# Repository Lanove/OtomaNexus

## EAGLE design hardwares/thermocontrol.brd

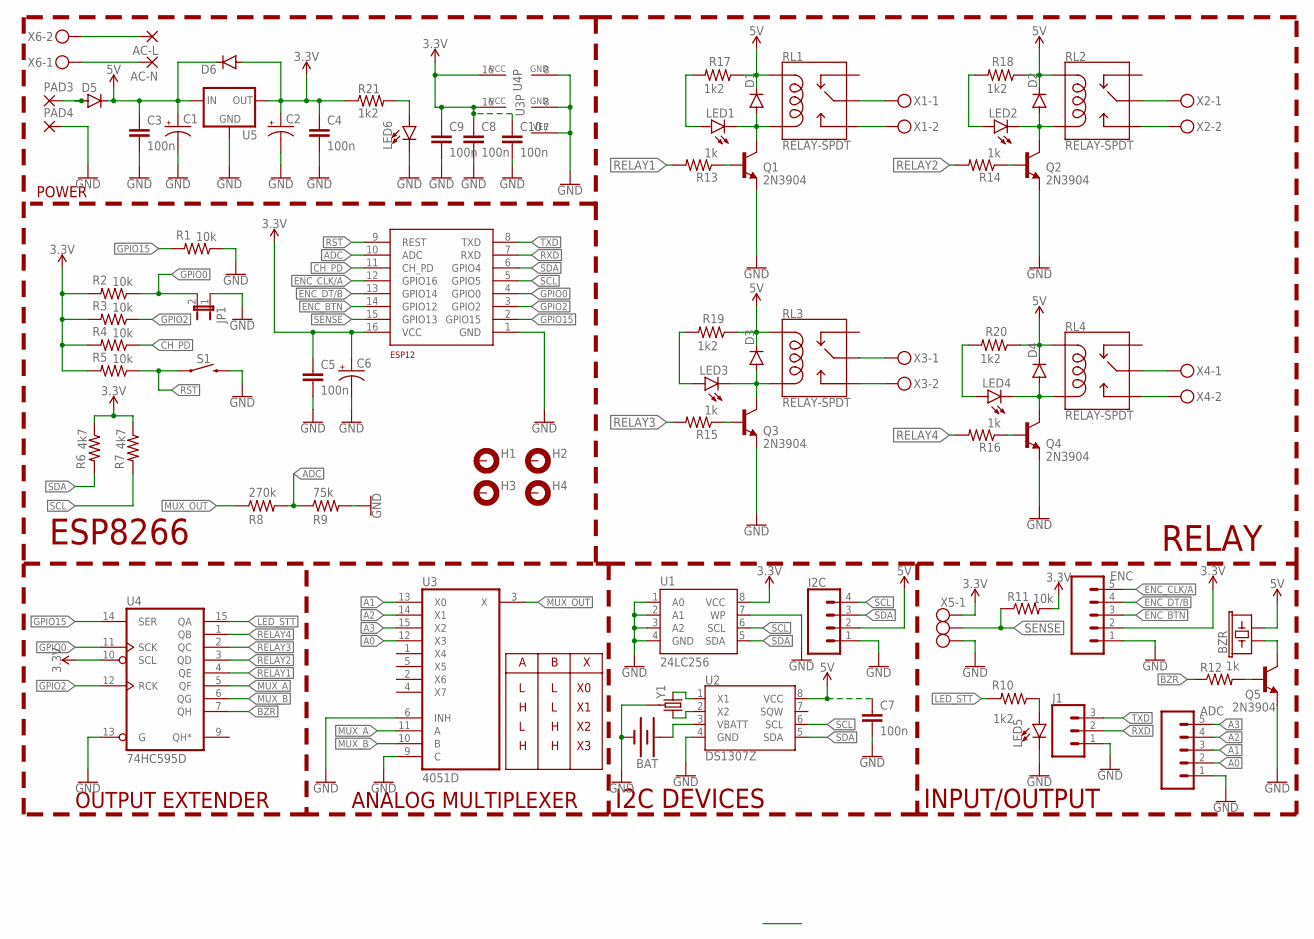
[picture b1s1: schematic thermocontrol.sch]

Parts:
AC-L: 2,54/1,1
AC-N: 2,54/1,1
ADC: CONN_05; 1X05
BAT: BATTERY-20MM_PTH_KIT; BATTCOM_20MM_PTH_KIT
BZR: BUZZER-PTH_KIT; BUZZER-12MM-KIT
C1, C2: CPOL-USE2.5-6; E2,5-6
C3, C4, C5, C7, C8, C9, C10: 100n; C0805
C6: CPOL-USD/7343-31R; D/7343-31R
D1, D2, D3, D4, D5, D6: DIODE-DO-214AC; DO-214AC
ENC: CONN_05; 1X05
ESP12: ESP8266_ESP-12; ESP8266-ESP12
H1, H2, H3, H4: MOUNT-PAD-ROUND2.8; 2,8-PAD
I2C: CONN_04PTH; 1X04
J1: 455-1750-1-ND; 1X03
JP1: JP1E; JP1
LED1, LED2, LED3, LED4, LED5, LED6: LEDCHIP-LED0805; CHIP-LED0805
PAD3, PAD4: 2,54/1,1
Q1, Q2, Q3, Q4, Q5: 2N3904; TO92
R1, R2, R3, R4, R5, R11: 10k; M0805
R6, R7: 4k7; M0805
R8: 270k; M0805
R9: 75k; M0805
R10, R17, R18, R19, R20, R21: 1k2; M0805
R12, R13, R14, R15, R16: 1k; M0805
RL1, RL2, RL3, RL4: RELAY-SPDT; RELAY_G5LE
S1: MOMENTARY-SWITCH-SPST-SMD-6.2MM-TALL; TACTILE_SWITCH_SMD_6.2MM_TALL
U1: 24LC256; SO08
U2: DS1307Z; SO08-0.15
U3: 4051D; SO16
U4: 74HC595D; SO16
U5: XC63FPP; SOT89R
X1, X2, X3, X4, X6: MKDSN1,5/2-5,08
X5: MKDSN1,5/3-5,08
Y1: CRYSTAL-32.768KHZ-CT; CRYSTAL-PTH-2X6-CYL

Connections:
3.3V: C2.+, C4.1, C5.1, C6.+, C8.1, C9.1, C10.1, D6.A, ENC.2, ESP12.16 (VCC), R2.2, R3.2, R4.2, R5.2, R6.1, R7.1, R11.2, R21.1, U1.8 (VCC), U3.16 (VCC), U4.10 (SCL), U4.16 (VCC), U5.3 (OUT), U5.4 (OUT), X5.1
5V: BZR.- (2), C1.+, C3.1, C7.1, D1.C, D2.C, D3.C, D4.C, D5.C, D6.C, I2C.2, R17.1, R18.1, R19.1, R20.1, RL1.2 (COIL1), RL2.2 (COIL1), RL3.2 (COIL1), RL4.2 (COIL1), U2.8 (VCC), U5.2 (IN)
A0: ADC.2, U3.12 (X3)
A1: ADC.3, U3.13 (X0)
A2: ADC.4, U3.14 (X1)
A3: ADC.5, U3.15 (X2)
ADC: ESP12.10 (ADC), R8.2, R9.1
BZR: R12.1, U4.7 (QH)
CH_PD: ESP12.11 (CH_PD), R4.1
ENC_BTN: ENC.3, ESP12.14 (GPIO12)
ENC_CLK/A: ENC.5, ESP12.12 (GPIO16)
ENC_DT/B: ENC.4, ESP12.13 (GPIO14)
GND: ADC.1, BAT.2 (-), C1.-, C2.-, C3.2, C4.2, C5.2, C6.-, C7.2, C8.2, C9.2, C10.2, ENC.1, ESP12.1 (GND), I2C.1, J1.1, JP1.1, LED5.C, LED6.C, PAD4.1, Q1.3 (E), Q2.3 (E), Q3.3 (E), Q4.3 (E), Q5.3 (E), R1.1, R9.2, S1.B2 (2), U1.1 (A0), U1.2 (A1), U1.3 (A2), U1.4 (GND), U2.4 (GND), U3.6 (INH), U3.7 (VEE), U3.8 (GND), U3.9 (C), U4.8 (GND), U4.13 (G), U5.1 (GND), X5.3, Y1.P$1 (GND)
GPIO0: ESP12.4 (GPIO0), JP1.2, R2.1, U4.11 (SCK)
GPIO2: ESP12.3 (GPIO2), R3.1, U4.12 (RCK)
GPIO15: ESP12.2 (GPIO15), R1.2, U4.14 (SER)
LED_STT: R10.2, U4.15 (QA)
MUX_A: U3.11 (A), U4.5 (QF)
MUX_B: U3.10 (B), U4.6 (QG)
MUX_OUT: R8.1, U3.3 (X)
unnamed: Q4.2 (B), R16.1
unnamed: Q2.2 (B), R14.1
unnamed: Q1.2 (B), R13.1
unnamed: Q3.2 (B), R15.1
unnamed: Q5.2 (B), R12.2
unnamed: LED1.A, R17.2
unnamed: LED2.A, R18.2
unnamed: D5.A, PAD3.1
unnamed: LED3.A, R19.2
unnamed: AC-N.1, X6.1
unnamed: AC-L.1, X6.2
unnamed: LED4.A, R20.2
unnamed: D1.A, LED1.C, Q1.1 (C), RL1.5 (COIL2)
unnamed: LED6.A, R21.2
unnamed: RL1.3 (NO), X1.2
unnamed: RL1.1 (MAIN), X1.1
unnamed: D2.A, LED2.C, Q2.1 (C), RL2.5 (COIL2)
unnamed: RL2.3 (NO), X2.2
unnamed: RL2.1 (MAIN), X2.1
unnamed: D3.A, LED3.C, Q3.1 (C), RL3.5 (COIL2)
unnamed: RL3.3 (NO), X3.2
unnamed: RL3.1 (MAIN), X3.1
unnamed: D4.A, LED4.C, Q4.1 (C), RL4.5 (COIL2)
unnamed: RL4.3 (NO), X4.2
unnamed: RL4.1 (MAIN), X4.1
unnamed: BAT.1 (+), U2.3 (VBATT)
unnamed: BZR.+ (1), Q5.1 (C)
unnamed: LED5.A, R10.1
unnamed: U2.2 (X2), Y1.2
unnamed: U2.1 (X1), Y1.1
RELAY1: R13.2, U4.4 (QE)
RELAY2: R14.2, U4.3 (QD)
RELAY3: R15.2, U4.2 (QC)
RELAY4: R16.2, U4.1 (QB)
RST: ESP12.9 (REST), R5.1, S1.A2 (1)
RXD: ESP12.7 (RXD), J1.2
SCL: ESP12.5 (GPIO5), I2C.4, R7.2, U1.6 (SCL), U2.6 (SCL)
SDA: ESP12.6 (GPIO4), I2C.3, R6.2, U1.5 (SDA), U2.5 (SDA)
SENSE: ESP12.15 (GPIO13), R11.1, X5.2
TXD: ESP12.8 (TXD), J1.3

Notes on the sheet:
OUTPUT EXTENDER
ANALOG MULTIPLEXER
INPUT/OUTPUT
ESP8266
RELAY
POWER
I2C DEVICES

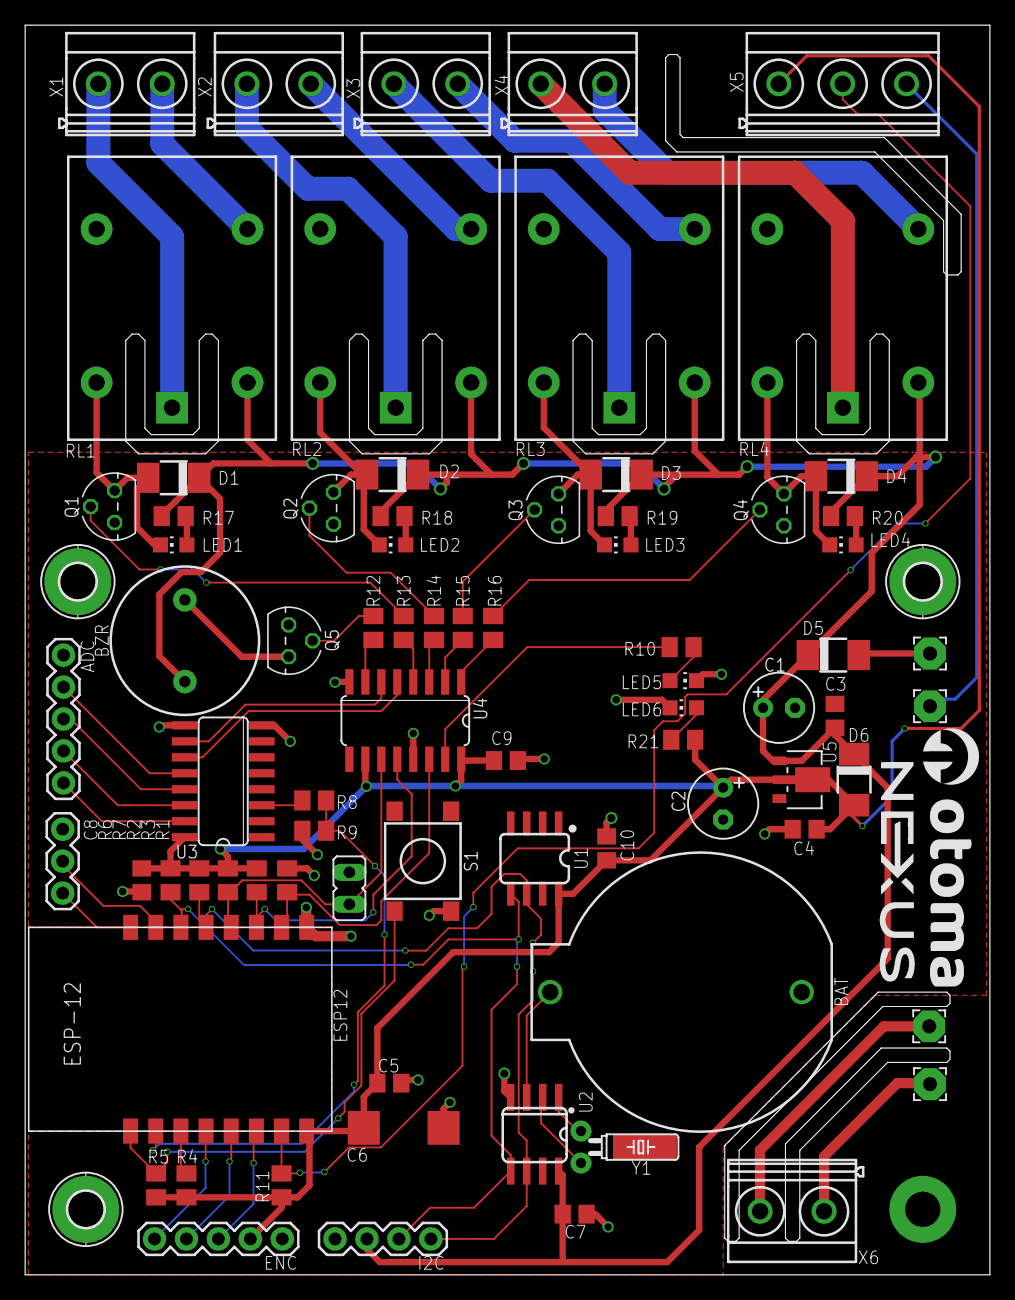
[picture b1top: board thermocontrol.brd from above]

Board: 2 copper layers, 76.7 x 99.4 mm, 81 parts (1 on the bottom side), 60 nets.

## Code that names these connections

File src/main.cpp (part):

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Ngubah keadaan output pas akhir program, kinda like ladder logic

Keterangan Pin :
- GPIO16 - ENC CLK/A
- GPIO14 - ENC DT/B
- GPIO12 - ENC BTN
- GPIO13 - SENSE
- GPIO0 - 595 CLK
- GPIO2 - 595 LATCH
- GPIO15 - 595 DATA

*/
#include <Arduino.h>
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
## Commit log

2020-10-08 First Build
2020-10-08 I2C EEPROM API Fix
2020-10-08 AES repair
2020-10-10 Revising Offline HTML Page and Auth System
2020-10-10 Revised Setup and Auth System
2020-10-10 Auth and Setup Revision Kansei
2020-10-12 Stack and Heap test
2020-10-12 Added RTC and NTP Synchronization
2020-10-12 Added some todo list and idea
2020-10-13 Added timeout no taiou
2020-10-14 Added 595 API and Reboot on WiFi fail connect.
2020-10-15 WifiClientSecure and proggress
2020-10-16 EEPROM Program API
2020-10-16 Update Temp,Humid and Graph to Web Server
2020-10-16 HTTP Persistent 1
2020-10-16 Prog Update Okay
2020-10-16 little tweak from last update
2020-10-17 Fetch update from server to EEPROM (untested)
2020-10-18 Error Proggress
2020-10-18 PID and Hysteresis Work (Heater, cooler untested)
2020-10-18 Added online status update
2020-10-19 Automation program implemented but imperfect
2020-10-20 Added DS18B notfound action, optimize first byte writing method, optimize ifs condition of thermocontrol, added esp build version and mac address
2020-10-20 Added progTrig 5 (Condition) and fixed progTrig 3 and 4 algorithm
2020-10-20 follow up fix
2020-10-20 Baseline program done (further testing is hitsuyou)
2020-10-22 Added Blinker class, Program Scanner changed to timer1 instead of ticker, add even more http info header
2020-10-22 Added Buzzer status, Fixes HTTP Header crash
2020-10-22 polished PID Algorithm
2020-10-23 Minor update to fix crashes caused by interrupt
2020-10-23 Followup minor fix
2020-10-23 HTTP Server Update
2020-10-23 Reverted programScanner handle to ticker for stability reason
2020-10-23 Improve code style, added periodic HTTPUpdate check
2020-10-24 Fixed minor program bug, added fallback and restart cmd
2020-10-24 Added LCD and Encoder Lib and test code (enc btn aimai)
2020-10-25 added lcd transition API
2020-10-25 lcd proggress untested
2020-10-25 lcd proggress (tested)
2020-10-26 Lcd dying?
2020-10-26 lcd fixed (i2c pins)
2020-10-26 screen 5 and screen 6 done (bug when encoder is scrolling fast)
2020-10-26 1.0.0 pre-production (debugging is important)
2020-10-27 added blank eeprom setup
2020-10-27 Added DS18B error catch (restart after 10 fail sample)
2020-10-27 Online Release 0.0.0
2020-10-28 Using BearSSL and session test
2020-10-28 SSL Fetch done
2020-10-28 Added some more LCD info, Reverted cloudflare cert to original jetorbit cert (fasterr)
2020-10-28 Add restart option to page 2 lcd Check update only when connected to wifi Add sensor sample interval
2020-10-29 Fix on LCD (Restart menu)
2020-10-29 LCD first page fix
2020-10-31 Fix DHT reading problem and Fix DHT Lcd display
2021-01-10 Removed every thermocontrol trace
2021-01-10 Added pemanas,pendingin,humidifier program and adjust some program code to new update
2021-01-21 Reverted back to HTTP connection
2021-01-24 LCD Fixes
2021-01-24 * Added manual switch of output on output page * Minor LCD Fix * Fixes program pemanas,pendingin,humidifier
2021-01-24 * Bugfix on jadwal harian and tanggal waktu program
2021-08-14 Final Commit KTI

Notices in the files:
parts and their libraries:
SparkFun-Electromechanical: Licensing: Creative Commons ShareAlike 4.0 International - https://creativecommons.org/licenses/by-sa/4.0
